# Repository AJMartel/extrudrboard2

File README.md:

# Extrudrboard2
Proposed revision of [Printrbot] [Extrudrboard] for
multi-color/multimaterial printing

Thing tracker at
https://cscott.github.io/thing-tracker/#/thing/737eb982-b77f-43e0-ae38-4fc30f3e3170

## Description

The latest revision of the [Printrboard] (REV F6) is mildly incompatible
with the original [Extrudrboard],
since the HOTEND A signal used by the Extrudrboard was disconnected
and used to provide an extruder fan output.

Also, multimaterial printing doesn't actually need all of the extra
hotend and thermistor inputs.

This repo contains a proposed "Extrudrboard2" which is compatible with
Printrboard REV F6 and provides up to four additional stepper outputs,
used for multimaterial bowden extruders.  The original Printrboard
extruder stepper is used for the direct drive just before the hotend,
and these additional Extrudrboard outputs are multiplexed and used for
the individual filament options.

As a bonus, I've thrown in a FAN2 output for owners of REV F5 and
earlier Printrboards, which adds an extruder fan output which works
identically to that on the REV F6 Printrboard.

The multiplexing scheme here is inspired by the "[Super Switch]" of
Prusa, and in fact basically the same [Marlin] code (`MK2_MULTIPLEXER`)
can be used.  One wrinkle is that the Printrboard extruder output
(we'll call it E0) wants to be a [Gear Head Extruder] with 127
steps/mm, while the individual bowden drivers (E1-E4, driven by the
Extrudrboard2) may be the lower cost 96 steps/mm [Alu Extruder]s --
or even the short-lived injection-molded plastic extruder.  So some
software cleverness is needed to allow multiplexing different
extruders with potentially different steps/mm rates.

There are two versions of the board here.  The [`Extrudrboard2-thunk.sch`]
files are an initial
prototype that allows you to connect two original Extrudrboards to the
Printrboard using the new multiplexing signal scheme.  It uses some
random logic ICs for the multiplexer that I just happened to have in
my toolbox.  There was a three-unit minimum order, so I've got a couple extra.  You
could also order this from [OSH Park] as shared project
[wLrvnUeh](https://oshpark.com/shared_projects/wLrvnUeh) -- warning,
boards are not yet tested!

If Printrbot decided to actually adopt this "project" as a "product",
they'd want something more like [`Extrudrboard2.sch`], which integrates the
four stepper drivers from the two old extrudrboards into a single new
board.  I actually reused as much as possible of the original
Extrudrboard schematic, components, and component packages, so this
should be highly compatible with whatever manufacturing process
Printrbot had for the original Extrudrboard.

<br clear="both" />

## Instructions

### Choose your build

If you have existing [Extrudrboard]s you wish to upgrade to the new
Extrudrboard2 functionality, use [`Extrudrboard2-thunk.sch`] with 1 or
2 original Extrudrboards connected.  If you are making new boards from
scratch, use [`Extrudrboard2.sch`].

### Assembling `Extrudrboard2-thunk`

Populating the PCB is straight-forward.  Three 7x2 0.1" male headers get
soldered in for "Printrboard", "Extrudrboard #1" and "Extrudrboard #2".
Add three bypass caps.  Values are somewhat flexible, but I used one 22uF
(primarily to decouple `FILWIDTH`) and two 0.1uF caps (to decouple the
logic ICs).  Solder in the 74HC138 and 74HC04; use DIP sockets if you like.
Note that the 74HC238 is actually a better fit here, but I just happened
to have a '138 in my toolbox so I added an inverter chip to make it work.
Likewise, you should feel free to use the LS or other variant of the logic
chips if you prefer: we're running on 5V and low speed, so any version
will do.

<br clear="both" />

### Wiring `Extrudrboard2-thunk`

Use three 2x7 header cables to connect the Printrboard and two Extrudrboards
as indicated.  The tricky part is keeping pin 1 on the cables oriented
correctly, especially as neither the Printrboard nor the Extrudrboards clearly
mark pin 1.

<br clear="both" />

You can connect a hotend fan to the HOTEND A output of Extrudrboard #1.
Pins 1 and 2 are shorted together, as are pins 3 and 4.  You probably
want to use a 1x2 female header on the center two pins.  I've marked
the polarity.

<br clear="both" />

### Additional features of `Extrudrboard2-thunk`

The `FILWIDTH` header is intended to support the Objects with Intelligence
[Filament Width Sensor](http://objectswithintelligence.weebly.com/store.html)
([thing:454584](https://www.thingiverse.com/thing:454584)), at the default
pin assignment used in upstream Marlin.  This is experimental: my
[multimaterial merge project](https://github.com/cscott/3d-multimaterial)
using the Extrudrboard2 doesn't have a place for this, and at the moment
I believe that minimizing distance between the merge and the gear head
drive is essential, so if I wanted to use it I'd likely have to significantly
re-engineer the filament width sensor to minimize the distance it would
add to the unsupported filament path.

The `EXPANSION` header brings all of the unused signals from both the
Printrboard EXP1 connector and the two Extrudrboard connectors into a
convenient place.  The 3 of the 4 HOTEND MOSFETs from the Extrudrboards
are unused (one is connected as an extruder fan output); it should be
convenient to use this header to wire them up to an unused signal from
EXP1 in order to drive some auxiliary load: extra lights, heaters, etc.

### Assembling `Extrudrboard2`

TBD...

### Wiring `Extrudrboard2`

TBD...

## Related

* [Forum discussion for this project](http://forum.monstercafe.net/topic5.html)
* [Multimaterial project](https://github.com/cscott/3d-multimaterial)
* [Repo for original Printrboard/Extruderboard](https://github.com/Printrbot/printrboard)

## License

These designs are released under the
[Creative Commons Attribution Share Alike 3.0] license, like the
original [Extrudrboard](https://github.com/Printrbot/printrboard#printrboard).

[Printrbot]: http://printrbot.com
[Printrboard]: http://reprap.org/wiki/Printrboard
[Extrudrboard]: http://reprap.org/wiki/Adding_more_extruders#RAMPS_using_ExtrudrBoard
[Marlin]: http://www.marlinfw.org/
[Super Switch]: https://github.com/prusa3d/Original-Prusa-i3/issues/29
[Gear Head Extruder]: https://printrbot.com/shop/gear-head-extruder-v2/
[Alu Extruder]: https://printrbot.com/shop/printrbot-alu-extruder-v2/
[`Extrudrboard2.sch`]: ./Extrudrboard2.sch.pdf
[`Extrudrboard2-thunk.sch`]: ./Extrudrboard2-thunk.sch.pdf
[OSH Park]: https://oshpark.com
[Creative Commons Attribution Share Alike 3.0]: https://spdx.org/licenses/CC-BY-SA-3.0.html

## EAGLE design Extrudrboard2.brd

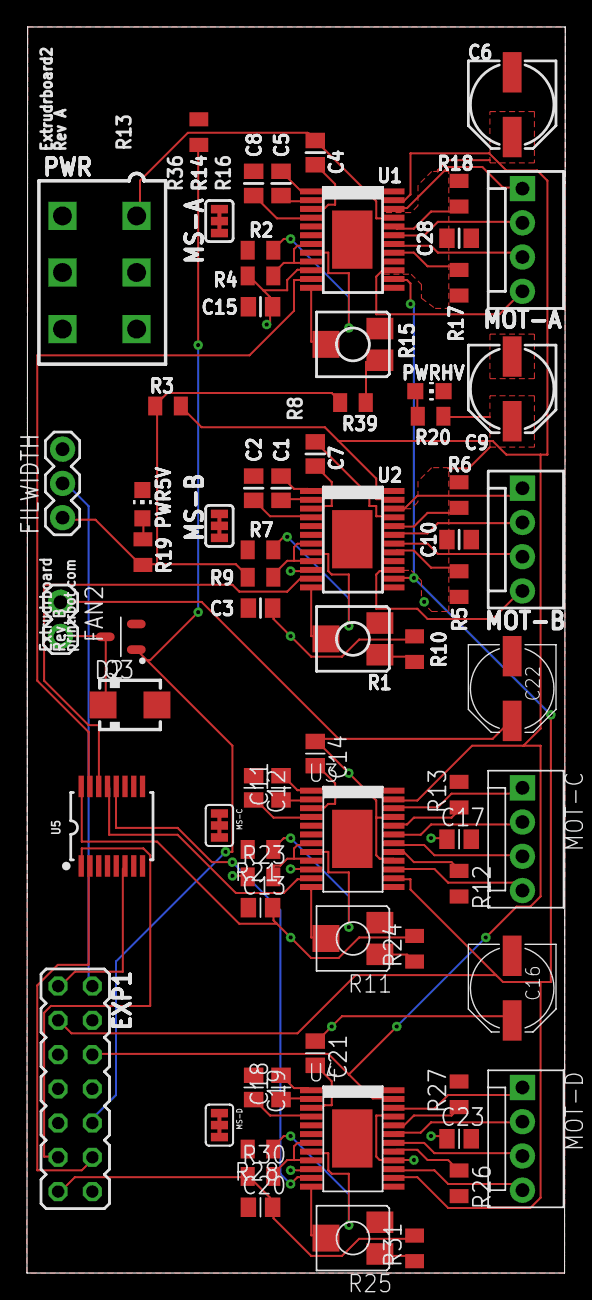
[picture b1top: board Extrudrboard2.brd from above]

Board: 4 copper layers, 39.9 x 92.4 mm, 73 parts (0 on the bottom side), 81 nets.

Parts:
C1, C4, C5, C7, C10, C11, C14, C17, C18, C21, C23, C28: 0.1uF; CAPC2012X145AN
C2, C8, C12, C19: 0.22uF; CAPC2012X145AN
C3, C13, C15, C20: 10uF; CAPC2012X145AN
C6, C9, C16, C22: 100uF; PANASONIC_D
D2: SMA
EXP1: PB-E1; JP7Q
FAN2: FAN; 1X02
FILWIDTH: FILWIDTH; 1X03
MOT-A: MOT-A; MOLEX-1X4
MOT-B: MOT-B; MOLEX-1X4
MOT-C: MOT-C; MOLEX-1X4
MOT-D: MOT-D; MOLEX-1X4
MS-A: SJ_3_CONNECTED
MS-B: SJ_3_CONNECTED
MS-C: SJ_3_CONNECTED
MS-D: SJ_3_CONNECTED
PWR: 5566-6
PWR5V: PWR; CHIP-LED0805
PWRHV: PWR; CHIP-LED0805
Q3: RFP30N06LE; SOT95P280X135-3N
R1, R11, R15, R25: 10k; RTRIM-ST4ETB
R2, R7, R21, R28: 10k; RESC2012X70N
R3, R4, R9, R14, R23, R30: 100k; RESC2012X70N
R5, R6, R12, R13, R17, R18, R26, R27: 0.11; RESC2012X70N
R10, R24, R31, R39: 20k; RESC2012X70N
R19: 330; RESC2012X70N
R20: 1k; RESC2012X70N
U1, U2, U3, U4: A4982; TSSOP-24
U5: MC74HC238ADTR2G; TSSOP16

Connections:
12V: C4.1, C6.+, C7.1, C9.+, C10.1, C14.1, C16.+, C17.1, C21.1, C22.+, C23.1, C28.1, FAN2.1, PWR.1, PWR.2, PWR.3, R20.2, U1.16, U1.21, U2.16, U2.21, U3.16, U3.21, U4.16, U4.21
!E-ENABLE: EXP1.6, R3.2, U1.23, U2.23, U3.23, U4.23
!PWM-FAN2: EXP1.10, Q3.1, R14.1
+5V: C3.2, C13.2, C15.2, C20.2, EXP1.13, FILWIDTH.1, MS-A.2, MS-B.2, MS-C.2, MS-D.2, R3.1, R4.1, R9.1, R10.2, R19.2, R23.1, R24.2, R30.1, R31.2, R39.2, U1.10, U2.10, U3.10, U4.10, U5.16
A-STEP: U1.11, U5.15
B-STEP: U2.11, U5.14
C-STEP: U3.11, U5.13
D-STEP: U4.11, U5.12
E-DIR: EXP1.3, U1.14, U2.14, U3.14, U4.14
E-MUX0: EXP1.11, U5.1
E-MUX1: EXP1.12, U5.2
E-STEP: EXP1.1, U5.6
FILWIDTH: EXP1.2, FILWIDTH.2
GND: C2.1, C3.1, C6.-, C8.1, C9.-, C10.2, C12.1, C13.1, C15.1, C16.-, C17.2, C19.1, C20.1, C22.-, C23.2, C28.2, D2.A, EXP1.14, FILWIDTH.3, PWR.4, PWR.5, PWR.6, PWR5V.C, PWRHV.C, Q3.2, R1.2, R2.2, R5.2, R6.2, R7.2, R11.2, R12.2, R13.2, R14.2, R15.2, R17.2, R18.2, R21.2, R25.2, R26.2, R27.2, R28.2, U1.13, U1.24, U1.PAD, U2.13, U2.24, U2.PAD, U3.13, U3.24, U3.PAD, U4.13, U4.24, U4.PAD, U5.3, U5.4, U5.5, U5.8
unnamed: C1.2, U2.1
unnamed: C1.1, U2.2
unnamed: R5.1, U2.17
unnamed: R6.1, U2.20
unnamed: R1.W, U2.12
unnamed: R7.1, U2.8
unnamed: C2.2, U2.4
unnamed: R9.2, U2.7, U2.9
unnamed: C7.2, U2.3
unnamed: MOT-A.3, U1.18
unnamed: C5.2, U1.1
unnamed: C5.1, U1.2
unnamed: R2.1, U1.8
unnamed: R17.1, U1.17
unnamed: R18.1, U1.20
unnamed: C4.2, U1.3
unnamed: MOT-A.4, U1.15
unnamed: R15.W, U1.12
unnamed: C8.2, U1.4
unnamed: MOT-A.2, U1.19
unnamed: R4.2, U1.7, U1.9
unnamed: MS-B.1, U2.5
unnamed: MOT-A.1, U1.22
unnamed: MS-B.3, U2.6
unnamed: MOT-B.3, U2.18
unnamed: MOT-B.4, U2.15
unnamed: MS-A.1, U1.5
unnamed: MS-A.3, U1.6
unnamed: MOT-B.2, U2.19
unnamed: MOT-B.1, U2.22
unnamed: R1.1, R10.1
unnamed: PWR5V.A, R19.1
unnamed: PWRHV.A, R20.1
unnamed: C11.2, U3.1
unnamed: C11.1, U3.2
unnamed: R12.1, U3.17
unnamed: R13.1, U3.20
unnamed: R11.W, U3.12
unnamed: R21.1, U3.8
unnamed: C12.2, U3.4
unnamed: R23.2, U3.7, U3.9
unnamed: C14.2, U3.3
unnamed: MS-C.1, U3.5
unnamed: MS-C.3, U3.6
unnamed: MOT-C.3, U3.18
unnamed: MOT-C.4, U3.15
unnamed: MOT-C.2, U3.19
unnamed: MOT-C.1, U3.22
unnamed: R11.1, R24.1
unnamed: C18.2, U4.1
unnamed: C18.1, U4.2
unnamed: R26.1, U4.17
unnamed: R27.1, U4.20
unnamed: R25.W, U4.12
unnamed: R28.1, U4.8
unnamed: C19.2, U4.4
unnamed: R30.2, U4.7, U4.9
unnamed: C21.2, U4.3
unnamed: MS-D.1, U4.5
unnamed: MS-D.3, U4.6
unnamed: MOT-D.3, U4.18
unnamed: MOT-D.4, U4.15
unnamed: MOT-D.2, U4.19
unnamed: MOT-D.1, U4.22
unnamed: R25.1, R31.1
unnamed: D2.C, FAN2.2, Q3.3
unnamed: R15.1, R39.1

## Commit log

2017-07-19 Initial board submission to OSH park. Multiplex the ENABLE lines.
2017-07-19 Multiplex STEP instead of ENABLE.
2017-07-21 Add PDFs of schematics for better browsability.
2017-07-21 Add link to forum discussion.
2017-07-25 Rename Extrudrboard to Extrudrboard2 for clarity.
2017-07-25 Add thing-tracker description.
2017-07-25 Add thumbnail images.
2017-07-31 Edits to README, relicense to CC-BY-SA-3.0.
2017-08-02 Add photos of assembled Extrudrboard2-thunk; describe assembly and wiring.

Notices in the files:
Extrudrboard2.brd:
Laine Walker-Avina (C) 2013
